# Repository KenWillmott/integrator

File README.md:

# integrator
Guitar pickup test instrument

The V5.8 integrator circuit provides a high impedance preamplifier, an integrator, and an output amplifier. It also has switches to control input gain, and to select between internally provided test loads. One of the loads is a large capacitor, to measure inductance, and the other is an RC load to simulate a typical guitar circuit. A three way switch can select between these two loads, or neither load in order to make an unloaded (actually minimally loaded) measurement.

For more details, read the wiki:
https://github.com/KenWillmott/integrator/wiki

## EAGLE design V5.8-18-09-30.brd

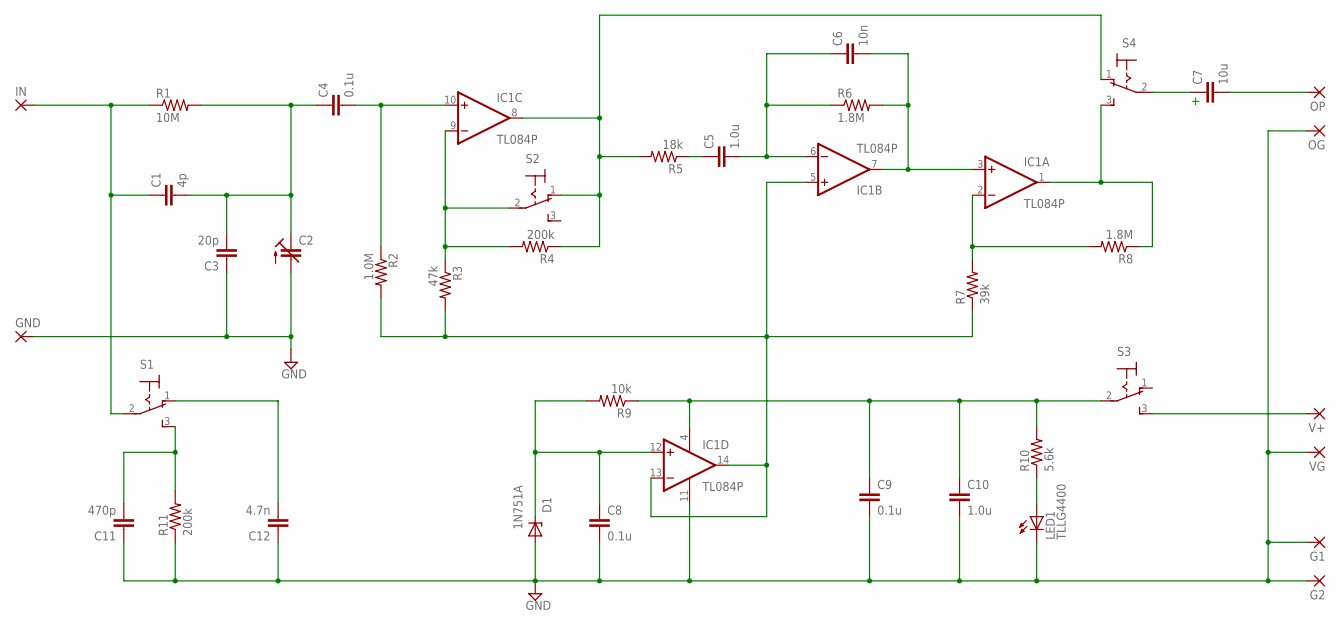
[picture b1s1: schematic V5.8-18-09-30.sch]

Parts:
C1: 4p; C050-024X044
C2: C-TRIMMGKG20015; GKG20015
C3: 20p; C050-024X044
C4, C8, C9: 0.1u; C050-024X044
C5, C10: 1.0u; C050-024X044
C6: 10n; C050-024X044
C7: 10u; C050-024X044
C11: 470p; C050-024X044
C12: 4.7n; C050-024X044
D1: ZENER-DIODEDO35Z10; DO35Z10
G1, G2: 2,54/1,1
GND: 2,54/1,1
IC1: TL084P; DIL14
IN: 2,54/1,1
LED1: TLLG4400; LED3MM
OG: 2,54/1,1
OP: 2,54/1,1
R1: 10M; 0207/10
R2: 1.0M; 0207/10
R3: 47k; 0207/10
R4, R11: 200k; 0207/10
R5: 18k; 0207/10
R6, R8: 1.8M; 0207/10
R7: 39k; 0207/10
R9: 10k; 0207/10
R10: 5.6k; 0207/10
S1, S2, S3, S4: 320-916
V+: 2,54/1,1
VG: 2,54/1,1

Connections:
GND: C2.1 (A), C3.1, C8.2, C9.2, C10.2, C11.1, C12.1, D1.A, G1.1, G2.1, GND.1, IC1.11 (V-), LED1.K (C), OG.1, R11.1, VG.1
IT: C12.2, S1.1 (O)
unnamed: LED1.A, R10.1
unnamed: C5.1, R5.1
unnamed: S3.3 (S), V+.1
unnamed: IC1.8 (OUT), R4.1, R5.2, S2.1 (O), S4.1 (O)
unnamed: IC1.9 (-IN), R3.1, R4.2, S2.2
unnamed: C6.2, IC1.3 (+IN), IC1.7 (OUT), R6.2
unnamed: IC1.2 (-IN), R7.2, R8.2
unnamed: IC1.1 (OUT), R8.1, S4.3 (S)
unnamed: C1.2, C2.2 (E), C3.2, C4.1, R1.2
unnamed: C8.1, D1.C, IC1.12 (+IN), R9.2
unnamed: C4.2, IC1.10 (+IN), R2.1
unnamed: C1.1, IN.1, R1.1, S1.2
unnamed: IC1.5 (+IN), IC1.13 (-IN), IC1.14 (OUT), R2.2, R3.2, R7.1
unnamed: C9.1, C10.1, IC1.4 (V+), R9.1, R10.2, S3.2
unnamed: C11.2, R11.2, S1.3 (S)
unnamed: C7.1, S4.2
unnamed: C5.2, C6.1, IC1.6 (-IN), R6.1
unnamed: C7.2, OP.1

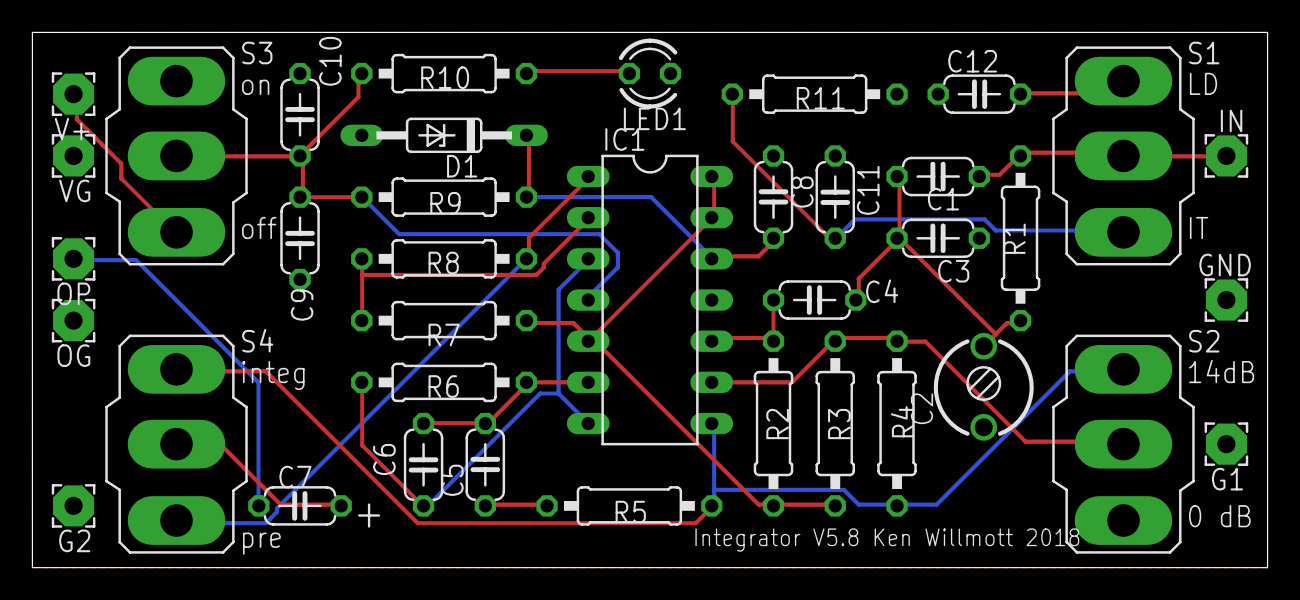
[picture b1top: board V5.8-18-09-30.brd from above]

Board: 2 copper layers, 76.2 x 33.0 mm, 38 parts (0 on the bottom side), 20 nets.

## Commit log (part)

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2018-09-29 fix incorrect screen for preamp gain label
2018-09-30 Add files via upload
    Corrected switch and trim cap dimensions and made board smaller
2018-10-06 completed for supplier Mouser Inc.
2018-10-14 add gerbers
2018-10-15 spreadsheet for results analysis
2019-05-20 Add manual for V5.8
2019-06-17 update BOM to reflect component changes on PCB
2019-07-08 correct errors in Mouser part numbers
2019-07-15 add device assembly guide
2019-07-27 updating schematic
2019-07-27 updating values to match BOM
2019-07-27 update values to match BOM
2019-07-27 add wiki link
2019-07-27 image for wiki
2019-08-19 replace C7 tantalum with MLCC and add cap markings
2020-05-18 minor updates to BOM
    change C10 from 1.0uF to 10uF
2021-03-27 Add instructions for building a test coil
2022-09-16 adding acrylic panel artwork
    reversed because you want to engrave the back of the panel not the front
